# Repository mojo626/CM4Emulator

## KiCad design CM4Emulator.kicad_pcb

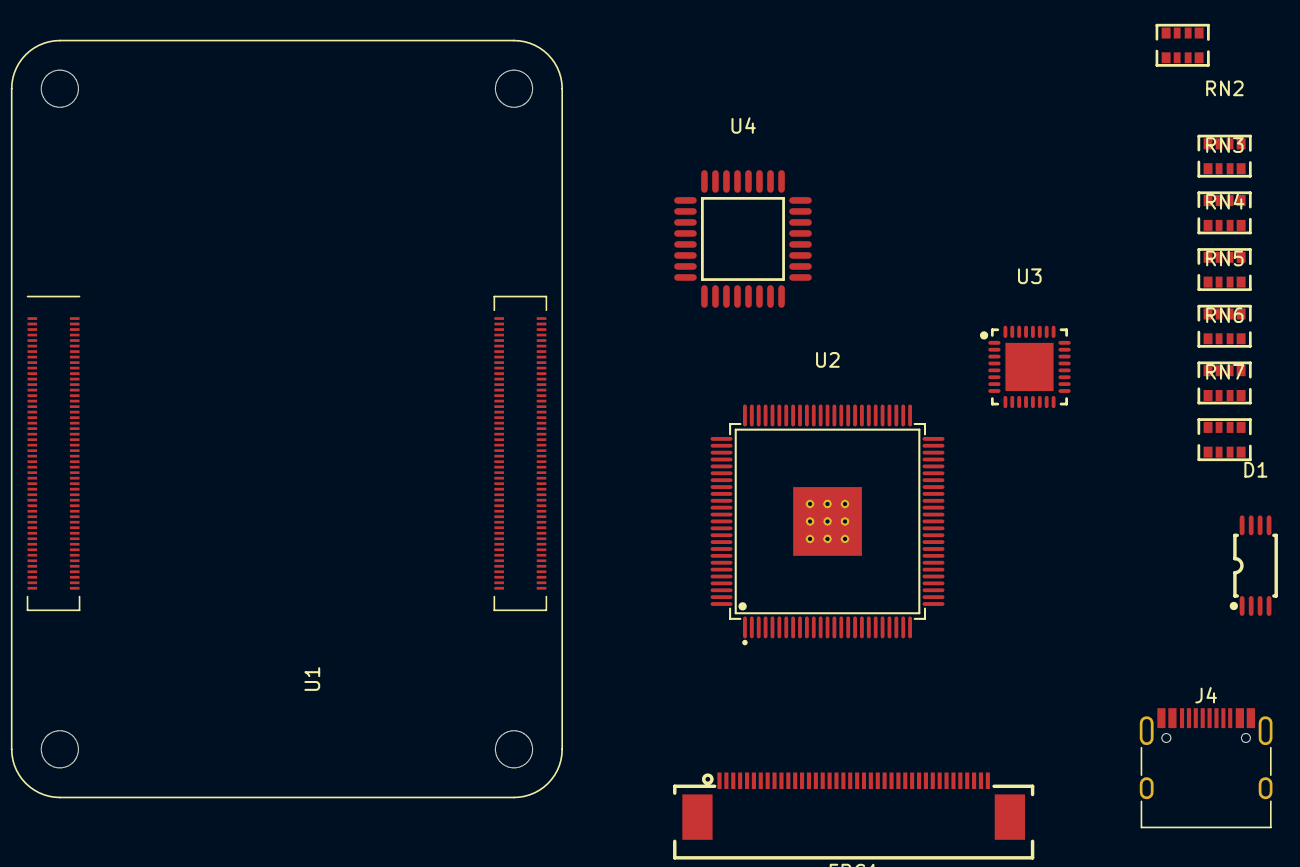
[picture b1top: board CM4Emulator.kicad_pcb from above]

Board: 2 copper layers, 14 parts (0 on the bottom side), 73 nets, no tracks yet.

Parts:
D1: SN75240PWR; TSSOP-8_L4.4-W3.0-P0.65-LS6.4-BL
FPC1: AFC07-S40ECA-00; FPC-SMD_P0.50-40P_LCS-SJ-H2.0
J4: USB_C_Receptacle_USB2.0; USB_C_Receptacle_HRO_TYPE-C-31-M-12
RN1, RN2, RN3, RN4, RN5, RN6, RN7: YC164-JR-0710KL; RES-ARRAY-SMD_0603-8P-L3.2-W1.6-BL
U1: Compute_Module_4_Functional; Raspberry-Pi-4-Compute-Module
U2: TFP401APZP; TQFP-100_L14.0-W14.0-P0.50-LS16.0-BL-EP5.2
U3: WM8960CGEFL/RV; QFN-32_L5.0-W5.0-P0.50-TL-EP
U4: TUSB2046BVFR; LQFP-32_L7.0-W7.0-P0.80-LS9.0-TL

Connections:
+1V8: U1.88 (CM4_1.8V_Out_1), U1.90 (CM4_1.8V_Out_2)
+3.3V: U1.84 (CM4_3.3V_Out_1), U1.86 (CM4_3.3V_Out_2), U3.8 (DCVDD), U3.10 (DBVDD), U3.21 (SPKVDD2), U3.26 (SPKVDD1), U3.32 (AVDD), U4.3 (VCC), U4.25 (VCC), U4.26 (~EXTMEM)
/Display/B0: RN5.5, U2.10 (QE0)
/Display/B1: RN5.6, U2.11 (QE1)
/Display/B2: RN5.7, U2.12 (QE2)
/Display/B3: RN5.8, U2.13 (QE3)
/Display/B4: RN6.5, U2.14 (QE4)
/Display/B5: RN6.6, U2.15 (QE5)
/Display/B6: RN6.7, U2.16 (QE6)
/Display/B7: RN6.8, U2.17 (QE7)
/Display/CLK: FPC1.30, RN7.3
/Display/DE: FPC1.34, RN7.4
/Display/G0: RN3.5, U2.20 (QE8)
/Display/G1: RN3.6, U2.21 (QE9)
/Display/G2: RN3.7, U2.22 (QE10)
/Display/G3: RN3.8, U2.23 (QE11)
/Display/G4: RN4.5, U2.24 (QE12)
/Display/G5: RN4.6, U2.25 (QE13)
/Display/G6: RN4.7, U2.26 (QE14)
/Display/G7: RN4.8, U2.27 (QE15)
/Display/HSYNC: FPC1.32, RN7.1
/Display/R0: RN1.5, U2.30 (QE16)
/Display/R1: RN1.6, U2.31 (QE17)
/Display/R2: RN1.7, U2.32 (QE18)
/Display/R3: RN1.8, U2.33 (QE19)
/Display/R4: RN2.5, U2.34 (QE20)
/Display/R5: RN2.6, U2.35 (QE21)
/Display/R6: RN2.7, U2.36 (QE22)
/Display/R7: RN2.8, U2.37 (QE23)
/Display/VSYNC: FPC1.33, RN7.2
GND: D1.1 (GND), D1.3 (GND), D1.5 (GND), D1.7 (GND), FPC1.3, FPC1.29, FPC1.36, J4.A1 (GND), J4.A12 (GND), J4.B1 (GND), J4.B12 (GND), J4.S1 (SHIELD), U1.1 (GND[51]), U1.2 (GND[51]), U1.7 (GND[51]), U1.8 (GND[51]), U1.13 (GND[51]), U1.14 (GND[51]), U1.22 (GND[51]), U1.23 (GND[51]), U1.32 (GND[51]), U1.33 (GND[51]), U1.42 (GND[51]), U1.43 (GND[51]), U1.52 (GND[51]), U1.53 (GND[51]), U1.59 (GND[51]), U1.60 (GND[51]), U1.65 (GND[51]), U1.66 (GND[51]), U1.71 (GND[51]), U1.74 (GND[51]), U1.98 (GND[51]), U1.107 (GND[51]), U1.108 (GND[51]), U1.113 (GND[51]), U1.114 (GND[51]), U1.119 (GND[51]), U1.120 (GND[51]), U1.125 (GND[51]), U1.126 (GND[51]), U1.131 (GND[51]), U1.132 (GND[51]), U1.137 (GND[51]), U1.138 (GND[51]), U1.144 (GND[51]), U1.150 (GND[51]), U1.155 (GND[51]), U1.156 (GND[51]), U1.161 (GND[51]), U1.162 (GND[51]), U1.167 (GND[51]), U1.168 (GND[51]), U1.173 (GND[51]), U1.174 (GND[51]), U1.179 (GND[51]), U1.180 (GND[51]), U1.185 (GND[51]), U1.186 (GND[51]), U1.191 (GND[51]), U1.192 (GND[51]), U1.197 (GND[51]), U1.198 (GND[51]), U2.5 (GND), U2.19 (OGND), U2.28 (OGND), U2.39 (GND), U2.45 (OGND), U2.58 (OGND), U2.68 (GND), U2.76 (OGND), U2.79 (AGND), U2.83 (AGND), U2.87 (AGND), U2.89 (AGND), U2.92 (AGND), U2.98 (PGND), U3.9 (DGND), U3.20 (SPKGND2), U3.24 (SPKGND1), U3.28 (AGND), U4.6 (EEDATA/GANGED), U4.7 (GND), U4.27 (TSTPLL/48MCLK), U4.28 (GND), U4.31 (TSTMODE)
HDMI0_CK+: U1.188 (HDMI0_CLK_P), U2.93 (RXC+)
HDMI0_CK-: U1.190 (HDMI0_CLK_N), U2.94 (RXC-)
HDMI0_D0+: U1.182 (HDMI0_TX0_P), U2.90 (RX0+)
HDMI0_D0-: U1.184 (HDMI0_TX0_N), U2.91 (RX0-)
HDMI0_D1+: U1.176 (HDMI0_TX1_P), U2.85 (RX1+)
HDMI0_D1-: U1.178 (HDMI0_TX1_N), U2.86 (RX1-)
HDMI0_D2+: U1.170 (HDMI0_TX2_P), U2.80 (RX2+)
HDMI0_D2-: U1.172 (HDMI0_TX2_N), U2.81 (RX2-)
unnamed: U2.6 (DVDD), U2.38 (DVDD), U2.67 (DVDD)
unnamed: U2.18 (OVDD), U2.29 (OVDD), U2.43 (OVDD), U2.57 (OVDD), U2.78 (OVDD)
unnamed: U2.82 (AVDD), U2.84 (AVDD), U2.88 (AVDD), U2.95 (AVDD)
unnamed: D1.8 (A), J4.A6 (D+), J4.B6 (D+)
unnamed: D1.6 (B), J4.A7 (D-), J4.B7 (D-)
unnamed: FPC1.5, RN1.4
unnamed: FPC1.6, RN1.3
unnamed: FPC1.7, RN1.2
unnamed: FPC1.8, RN1.1
unnamed: FPC1.9, RN2.4
unnamed: FPC1.10, RN2.3
unnamed: FPC1.11, RN2.2
unnamed: FPC1.12, RN2.1
unnamed: FPC1.13, RN3.4
unnamed: FPC1.14, RN3.3
unnamed: FPC1.15, RN3.2
unnamed: FPC1.16, RN3.1
unnamed: FPC1.17, RN4.4
unnamed: FPC1.18, RN4.3
unnamed: FPC1.19, RN4.2
unnamed: FPC1.20, RN4.1
unnamed: FPC1.21, RN5.4
unnamed: FPC1.22, RN5.3
unnamed: FPC1.23, RN5.2
unnamed: FPC1.24, RN5.1
unnamed: FPC1.25, RN6.4
unnamed: FPC1.26, RN6.3
unnamed: FPC1.27, RN6.2
unnamed: FPC1.28, RN6.1
unnamed: RN7.5, U2.46 (DE)
unnamed: RN7.8, U2.48 (HSYNC)
unnamed: RN7.6, U2.44 (ODCK)
unnamed: RN7.7, U2.47 (VSYNC)
VBUS: J4.A4 (VBUS), J4.A9 (VBUS), J4.B4 (VBUS), J4.B9 (VBUS)

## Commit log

2024-03-19 added display things + others
2024-03-20 audio and display changes
2024-03-21 more display things
2024-03-22 power changes
